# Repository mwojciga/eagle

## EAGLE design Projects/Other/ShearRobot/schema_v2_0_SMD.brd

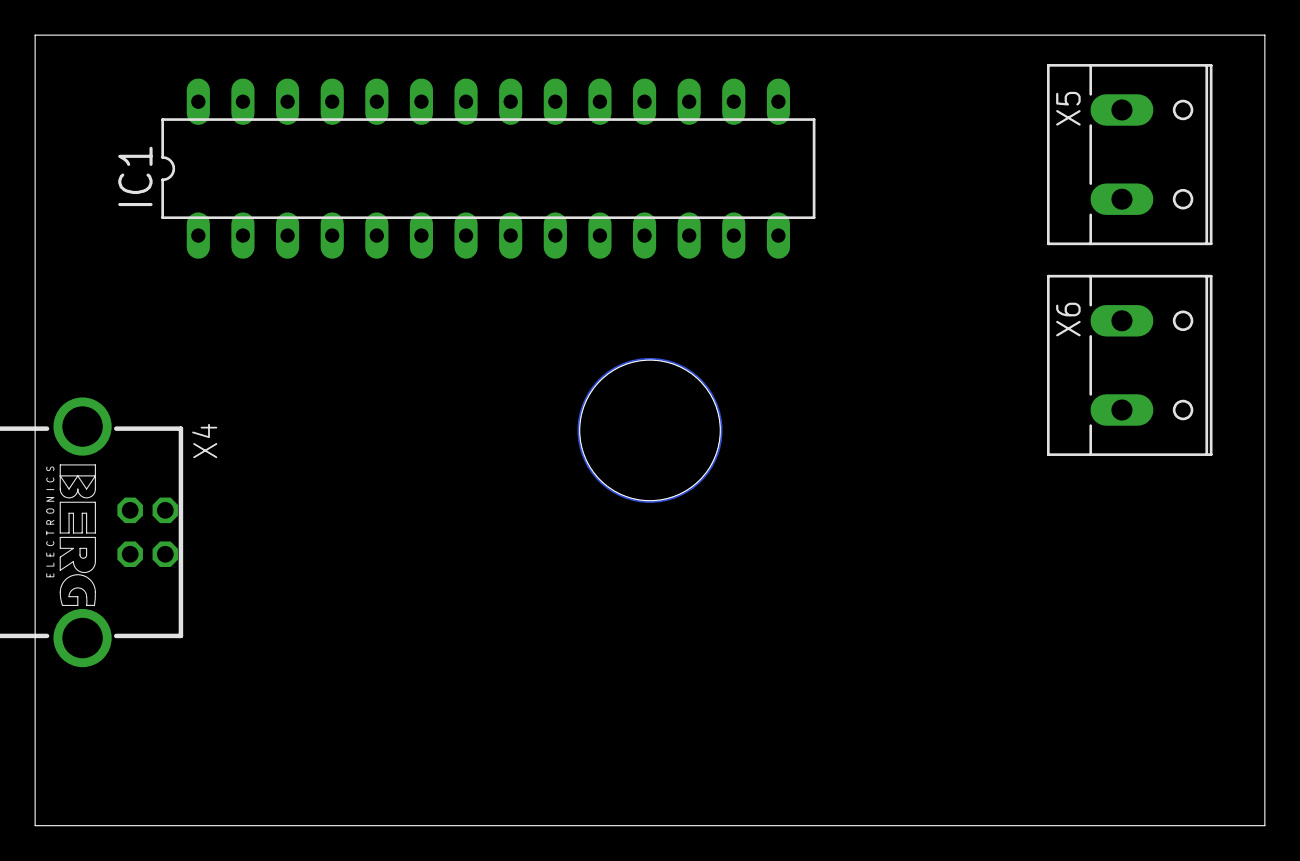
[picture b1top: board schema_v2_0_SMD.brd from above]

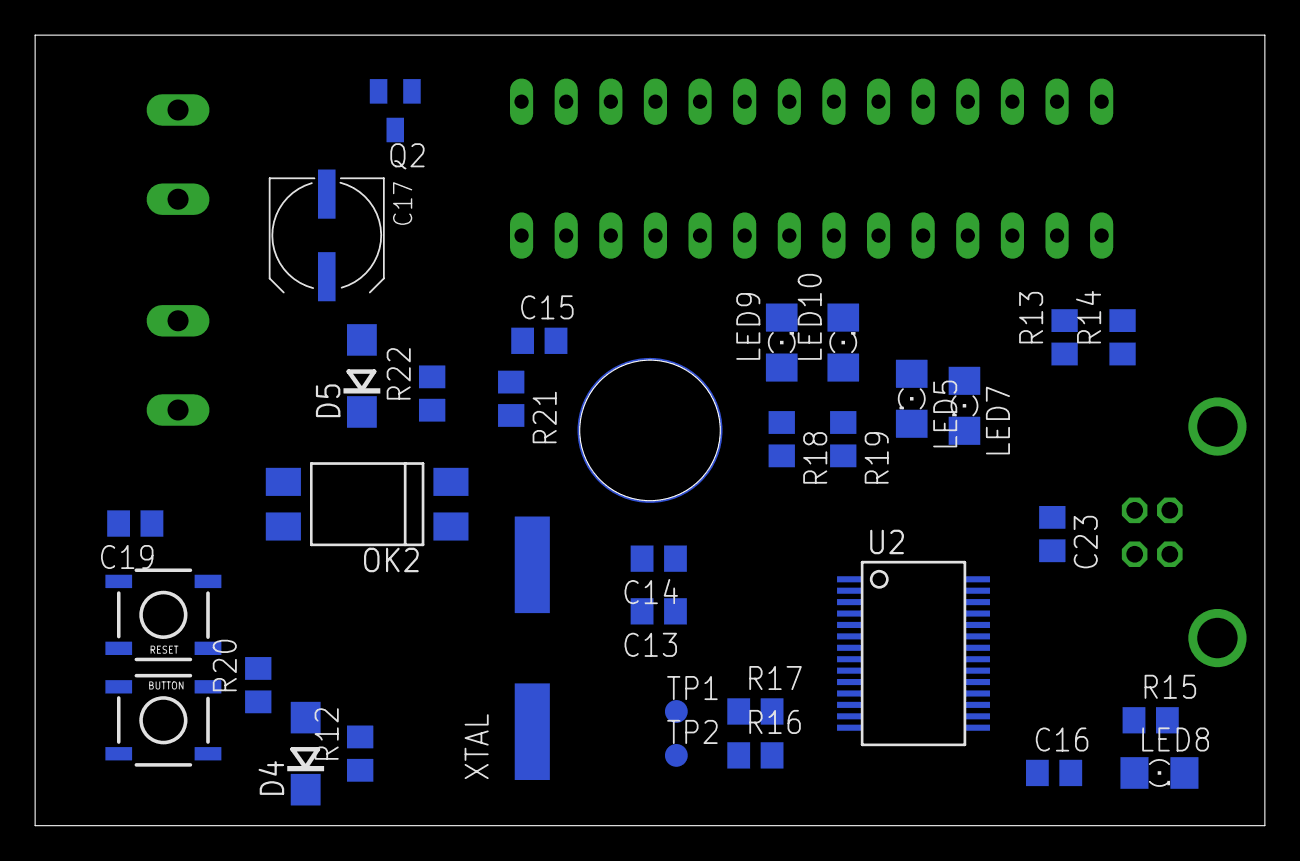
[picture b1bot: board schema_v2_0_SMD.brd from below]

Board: 2 copper layers, 70.0 x 45.0 mm, 37 parts (33 on the bottom side), 31 nets, no tracks yet.

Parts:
BUTTON: TACTILE_SWITCH_SMD
C13, C14: 22pF; C0805
C15, C16, C19, C23: 100nF; C0805
C17: UD-6,3X5,8_NICHICON
D4, D5: GS1B; DO214AC
IC1: MEGA8-P; DIL28-3
LED5, LED7, LED8, LED9, LED10: 1206
OK2: SFH6206; DIL4-SMD
Q2: BC817-16SMD; SOT23-BEC
R12: 22k; R0805
R13, R14, R15, R18, R19, R20: 330; R0805
R16, R17, R21: 1k; R0805
R22: 10k; R0805
RESET: TACTILE_SWITCH_SMD
TP1, TP2: TPTP13R; TP13R
U2: SSOP28DB
X4: PN61729-S
X5, X6: W237-132
XTAL: 16MHZ; CSM-7X-DU

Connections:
5V: C15.1, C23.2, D4.C, IC1.7, IC1.20, R12.1, R13.2, R14.2, R15.2, U2.4, U2.19, U2.20, X4.1
GND: BUTTON.1, BUTTON.2, C13.1, C14.1, C15.2, C16.2, C19.2, C23.1, IC1.8, IC1.22, LED8.C, LED9.C, LED10.C, OK2.2, RESET.3, RESET.4, U2.26, X4.4, X4.S1, X4.S2
unnamed: IC1.2, R16.1, TP2.TP
unnamed: IC1.3, R17.1, TP1.TP
unnamed: C19.1, IC1.21
unnamed: C14.2, IC1.10, XTAL.2
unnamed: C13.2, IC1.9, XTAL.1
unnamed: D4.A, IC1.1, R12.2, RESET.1, RESET.2
unnamed: LED5.A, R13.1
unnamed: LED7.A, R14.1
unnamed: LED5.C, U2.23
unnamed: LED7.C, U2.22
unnamed: R16.2, U2.5
unnamed: R17.2, U2.1
unnamed: BUTTON.3, BUTTON.4, R20.1
unnamed: IC1.6, R18.2
unnamed: U2.16, X4.2
unnamed: U2.15, X4.3
unnamed: IC1.5, R19.2
unnamed: LED8.A, R15.1
unnamed: IC1.23, R20.2
unnamed: C16.1, U2.17
unnamed: LED9.A, R18.1
unnamed: LED10.A, R19.1
unnamed: OK2.3, Q2.B
unnamed: OK2.1, R21.1
unnamed: IC1.11, R21.2
unnamed: OK2.4, R22.2
unnamed: C17.+, D5.C, R22.1, X5.2, X6.2
unnamed: C17.-, D5.A, Q2.C, X6.1
unnamed: Q2.E, X5.1

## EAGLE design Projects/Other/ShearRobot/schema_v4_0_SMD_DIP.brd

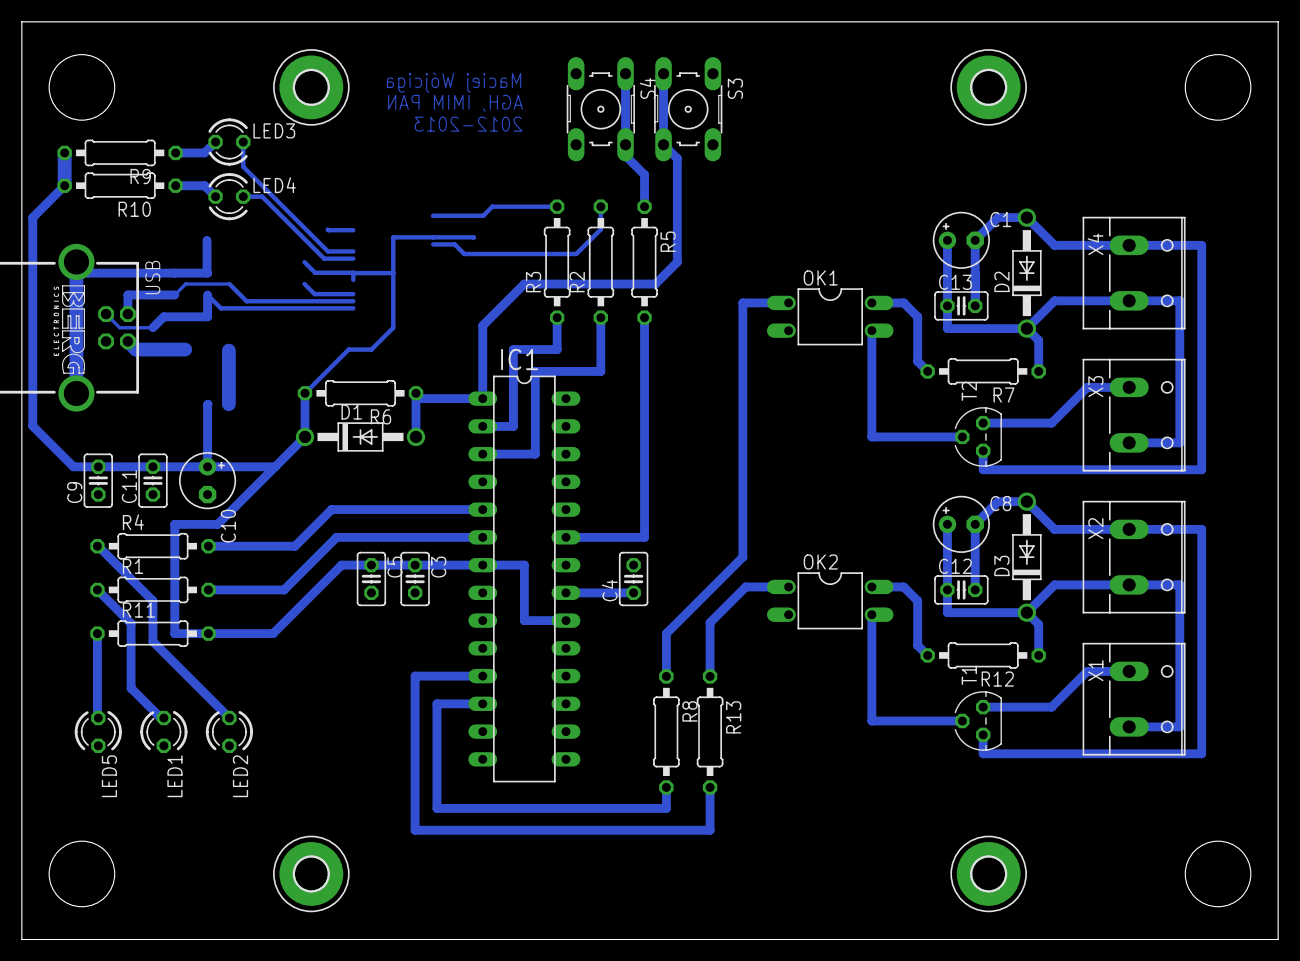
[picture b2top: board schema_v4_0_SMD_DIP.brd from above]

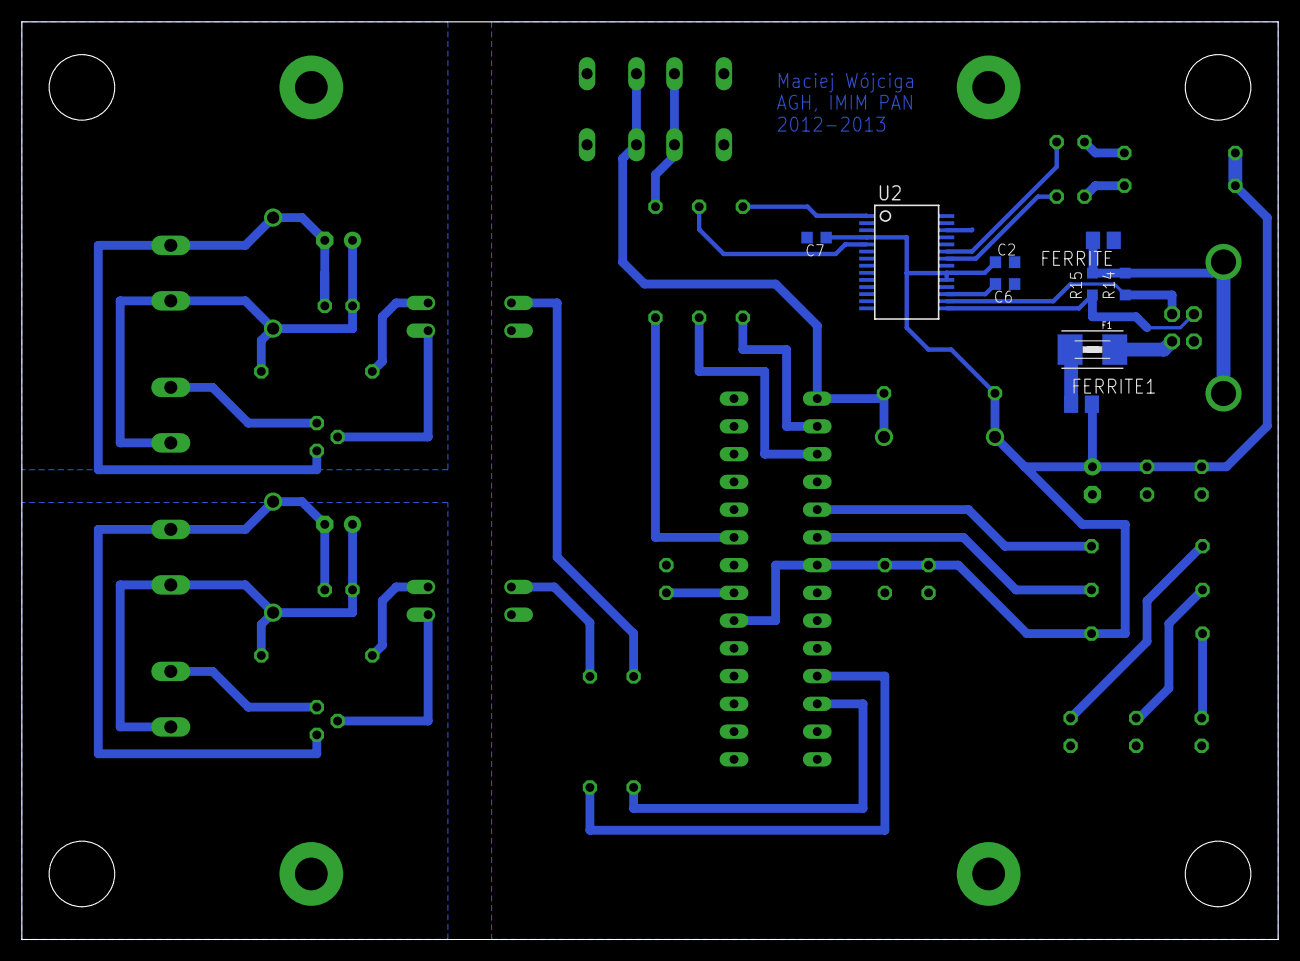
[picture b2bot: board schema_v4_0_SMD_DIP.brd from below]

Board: 2 copper layers, 115.0 x 84.0 mm, 56 parts (9 on the bottom side), 39 nets.

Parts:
C1, C8, C10: 1uF; E2,5-5
C2, C6, C7: 100nF; C0603K
C3, C4, C5, C9, C11, C12, C13: 100nF; C025-025X050
D1, D2, D3: 1N4001; DO41-10
F1: 1812
FERRITE, FERRITE1: M0805
H1, H2, H3, H4: MOUNT-PAD-ROUND3.0; 3,0-PAD
IC1: MEGA8-P; DIL28-3
LED1, LED2, LED3, LED4, LED5: LED3MM
OK1, OK2: LTV816; DIL04
R1, R4, R9, R10, R11: 330; 0207/10
R2, R3, R8, R13: 1k; 0207/10
R5, R7, R12: 10k; 0207/10
R6: 22k; 0207/10
R14, R15: VARISTORCN0603; CT/CN0603
S3, S4: B3F-10XX
T1, T2: BC547; TO92
U2: SSOP28DB
USB: PN61729-S
X1, X2, X3, X4: W237-132

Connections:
5V0: C2.1, C3.1, C5.1, C7.1, C9.2, C10.+, C11.2, D1.C, FERRITE1.2, IC1.7, IC1.20, R6.2, R9.2, R10.2, R11.2, U2.4, U2.19, U2.20
GND: C2.2, C3.2, C4.2, C5.2, C6.1, C7.2, C9.1, C10.-, C11.1, FERRITE.1, IC1.8, IC1.22, LED1.K, LED2.K, LED5.K, OK1.2, OK2.2, S3.1, S3.2, S4.3, S4.4, U2.26, USB.4
MOTOR1: IC1.11, R13.2
MOTOR2: IC1.12, R8.2
unnamed: IC1.3, R2.1
unnamed: IC1.2, R3.1
unnamed: C4.1, IC1.21
unnamed: IC1.23, R5.2
unnamed: LED1.A, R1.1
unnamed: LED2.A, R4.1
unnamed: D1.A, IC1.1, R6.1, S3.3, S3.4
unnamed: LED3.A, R9.1
unnamed: LED4.A, R10.1
unnamed: LED5.A, R11.1
unnamed: C1.+, C13.1, D2.C, R7.1, X3.2, X4.2
unnamed: OK2.1, R13.1
unnamed: C1.-, C13.2, D2.A, T2.3, X4.1
unnamed: OK1.3, T2.2
unnamed: OK2.4, R12.2
unnamed: T1.1, X1.1
unnamed: C8.+, C12.1, D3.C, R12.1, X1.2, X2.2
unnamed: C8.-, C12.2, D3.A, T1.3, X2.1
unnamed: OK2.3, T1.2
unnamed: F1.1, USB.1
unnamed: FERRITE.2, R14.2, R15.2, USB.S1, USB.S2
unnamed: F1.2, FERRITE1.1
unnamed: LED3.K, U2.23
unnamed: LED4.K, U2.22
unnamed: R5.1, S4.1, S4.2
unnamed: IC1.6, R1.2
unnamed: IC1.5, R4.2
unnamed: C6.2, U2.17
unnamed: OK1.1, R8.1
unnamed: OK1.4, R7.2
unnamed: T2.1, X3.1
RXD: R3.2, U2.1
TXD: R2.2, U2.5
USBDM: R14.1, U2.16, USB.2
USBDP: R15.1, U2.15, USB.3

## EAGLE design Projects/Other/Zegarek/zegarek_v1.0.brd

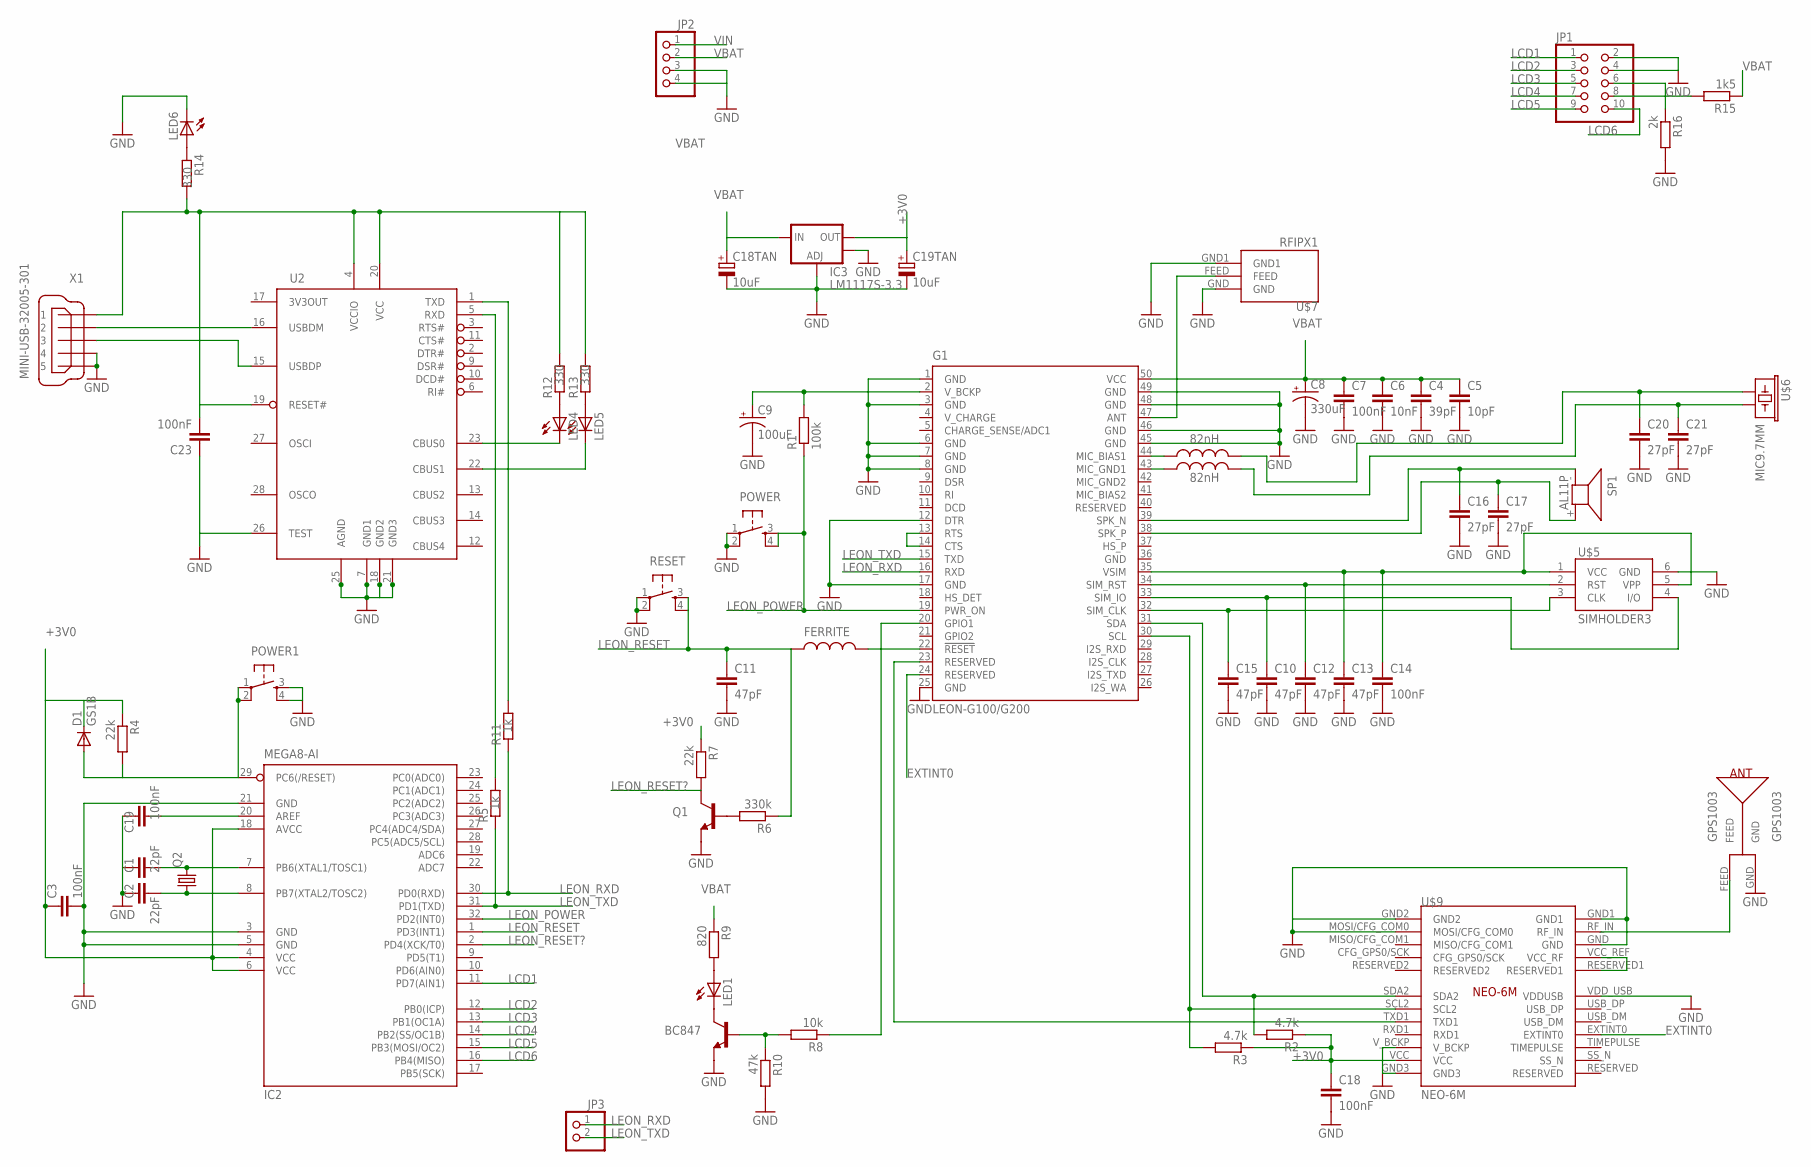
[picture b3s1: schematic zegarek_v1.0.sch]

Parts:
BC847: TRANSISTOR_NPNSOT23; SOT23
C1, C2: 22pF; C0805
C3, C7, C14, C18, C19, C23: 100nF; C0805
C4: 39pF; C0805
C5: 10pF; C0805
C6: 10nF; C0805
C8: 330uF; TT2D6
C9: 100uF; TT2D6
C10, C11, C12, C13, C15: 47pF; C0805
C16, C17, C20, C21: 27pF; C0805
C18TAN, C19TAN: 10uF; SMC_A
D1: GS1B; DO214AC
FERRITE: INDUCTOR0805; 0805
FERRITE1, FERRITE2: 82nH; 0805
G1: LEON-G100/G200
GPS1003: GPS1003
IC2: MEGA8-AI; TQFP32-08
IC3: LM1117S-3.3; SOT223
JP1: PINHD-2X5; 2X05
JP2: PINHD-1X4; 1X04
JP3: PINHD-1X2; 1X02
LED1, LED4, LED5, LED6: LEDSMT1206; 1206
POWER, POWER1: TAC_SWITCHSMD; TACTILE_SWITCH_SMD
Q1: TRANSISTOR_NPNSOT23; SOT23
Q2: CRYSTALHC49S; HC49/S
R1: 100k; R0805
R2, R3: 4.7k; R0805
R4, R7: 22k; R0805
R5, R11: 1k; R0805
R6: 330k; R0805
R8: 10k; R0805
R9: 820; R0805
R10: 47k; R0805
R12, R13, R14: 330; R0805
R15: 1k5; R0805
R16: 2k; R0805
RESET: TAC_SWITCHSMD; TACTILE_SWITCH_SMD
SP1: AL11P
U2: FT232RL; SSOP28DB
U$5: SIMHOLDER3
U$6: MIC9.7MM; MIC-9.7MM
U$7: RFIPX1; RF-IPX1
U$9: NEO-6M
X1: MINI-USB-32005-301; 32005-301

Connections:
+3V0: C3.1, C18.1, C19TAN.+, D1.C, IC2.4 (VCC), IC2.6 (VCC), IC2.18 (AVCC), IC3.2 (OUT), R2.1, R3.1, R4.1, R7.1, U$9.VCC
EXTINT0: G1.24 (RESERVED), U$9.EXTINT0
GND: BC847.2 (E), C1.1, C2.1, C3.2, C4.2, C5.2, C6.2, C7.2, C8.-, C9.-, C10.2, C11.2, C12.2, C13.2, C14.2, C15.2, C16.2, C17.2, C18.2, C18TAN.-, C19.2, C19TAN.-, C20.2, C21.2, C23.1, G1.1 (GND), G1.3 (GND), G1.6 (GND), G1.7 (GND), G1.8 (GND), G1.12 (DTR), G1.17 (GND), G1.25 (GND), G1.36 (GND), G1.45 (GND), G1.46 (GND), G1.48 (GND), G1.49 (GND), GPS1003.GND, IC2.3 (GND), IC2.5 (GND), IC2.21 (GND), IC3.1 (ADJ), IC3.4 (OUT), JP1.2, JP1.4, JP2.3, LED6.C, POWER.1, POWER.2, POWER1.3, POWER1.4, Q1.2 (E), R10.2, R16.2, RESET.1, RESET.2, U2.7 (GND1), U2.18 (GND2), U2.21 (GND3), U2.25 (AGND), U2.26 (TEST), U$5.6 (GND), U$7.GND, U$7.GND1, U$9.GND, U$9.GND1, U$9.GND2, U$9.GND3, U$9.MOSI/CFG_COM0, U$9.VDD_USB (VDDUSB), U$9.V_BCKP, X1.4, X1.5
LCD1: IC2.11 (PD7(AIN1)), JP1.1
LCD2: IC2.12 (PB0(ICP)), JP1.3
LCD3: IC2.13 (PB1(OC1A)), JP1.5
LCD4: IC2.14 (PB2(SS/OC1B)), JP1.7
LCD5: IC2.15 (PB3(MOSI/OC2)), JP1.9
LCD6: IC2.16 (PB4(MISO)), JP1.10
LEON_POWER: G1.19 (PWR_ON), IC2.32 (PD2(INT0)), POWER.3, POWER.4, R1.1
LEON_RESET: C11.1, FERRITE.1, IC2.1 (PD3(INT1)), R6.1, RESET.3, RESET.4
LEON_RESET?: IC2.2 (PD4(XCK/T0)), Q1.3 (C), R7.2
LEON_RXD: G1.16 (RXD), IC2.30 (PD0(RXD)), JP3.1, R11.1
LEON_TXD: G1.15 (TXD), IC2.31 (PD1(TXD)), JP3.2, R5.1
unnamed: FERRITE.2, G1.22 (!RESET)
unnamed: C2.2, IC2.8 (PB7(XTAL2/TOSC2)), Q2.1
unnamed: C9.+, G1.2 (V_BCKP), R1.2
unnamed: C13.1, C14.1, G1.35 (VSIM), U$5.1 (VCC), U$5.5 (VPP)
unnamed: C15.1, G1.32 (SIM_CLK), U$5.3 (CLK)
unnamed: C12.1, G1.34 (SIM_RST), U$5.2 (RST)
unnamed: C16.1, G1.39 (SPK_N), SP1.- (1)
unnamed: C10.1, G1.33 (SIM_IO), U$5.4 (I/O)
unnamed: C17.1, G1.38 (SPK_P), SP1.+ (2)
unnamed: G1.13 (RTS), G1.14 (CTS)
unnamed: FERRITE1.1, G1.44 (MIC_BIAS1)
unnamed: FERRITE2.1, G1.43 (MIC_GND1)
unnamed: C20.1, FERRITE1.2, U$6.1
unnamed: C21.1, FERRITE2.2, U$6.2
unnamed: Q1.1 (B), R6.2
unnamed: BC847.1 (B), R8.2, R10.1
unnamed: LED1.A, R9.2
unnamed: BC847.3 (C), LED1.C
unnamed: G1.20 (GPIO1), R8.1
unnamed: G1.47 (ANT), U$7.FEED
unnamed: JP1.6, R16.1
unnamed: GPS1003.FEED, U$9.RF_IN
unnamed: G1.31 (SDA), R2.2, U$9.SDA2
unnamed: U$9.RESERVED1, U$9.VCC_REF (VCC_RF)
unnamed: G1.30 (SCL), R3.2, U$9.SCL2
unnamed: G1.23 (RESERVED), U$9.TXD1
unnamed: C1.2, IC2.7 (PB6(XTAL1/TOSC1)), Q2.2
unnamed: D1.A, IC2.29 (PC6(/RESET)), POWER1.1, POWER1.2, R4.2
unnamed: C19.1, IC2.20 (AREF)
unnamed: LED4.A, R12.1
unnamed: LED5.A, R13.1
unnamed: LED4.C, U2.23 (CBUS0)
unnamed: LED5.C, U2.22 (CBUS1)
unnamed: R11.2, U2.1 (TXD)
unnamed: R5.2, U2.5 (RXD)
unnamed: JP1.8, R15.2
unnamed: C23.2, R12.2, R13.2, R14.2, U2.4 (VCCIO), U2.19 (RESET#), U2.20 (VCC), X1.1
unnamed: U2.16 (USBDM), X1.2
unnamed: U2.15 (USBDP), X1.3
unnamed: LED6.A, R14.1
VBAT: C4.1, C5.1, C6.1, C7.1, C8.+, C18TAN.+, G1.50 (VCC), IC3.3 (IN), JP2.2, R9.1, R15.1
VIN: JP2.1

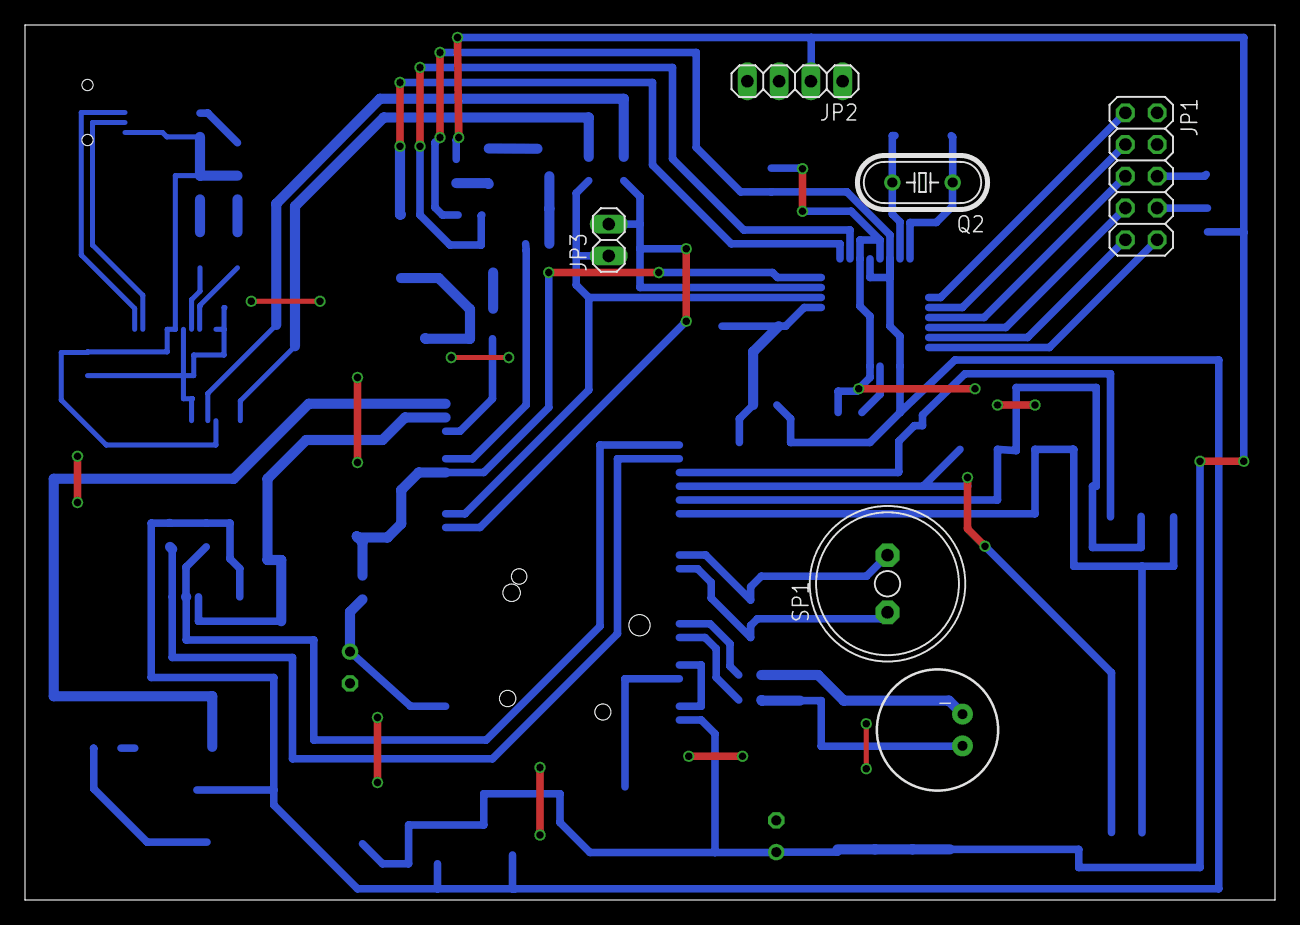
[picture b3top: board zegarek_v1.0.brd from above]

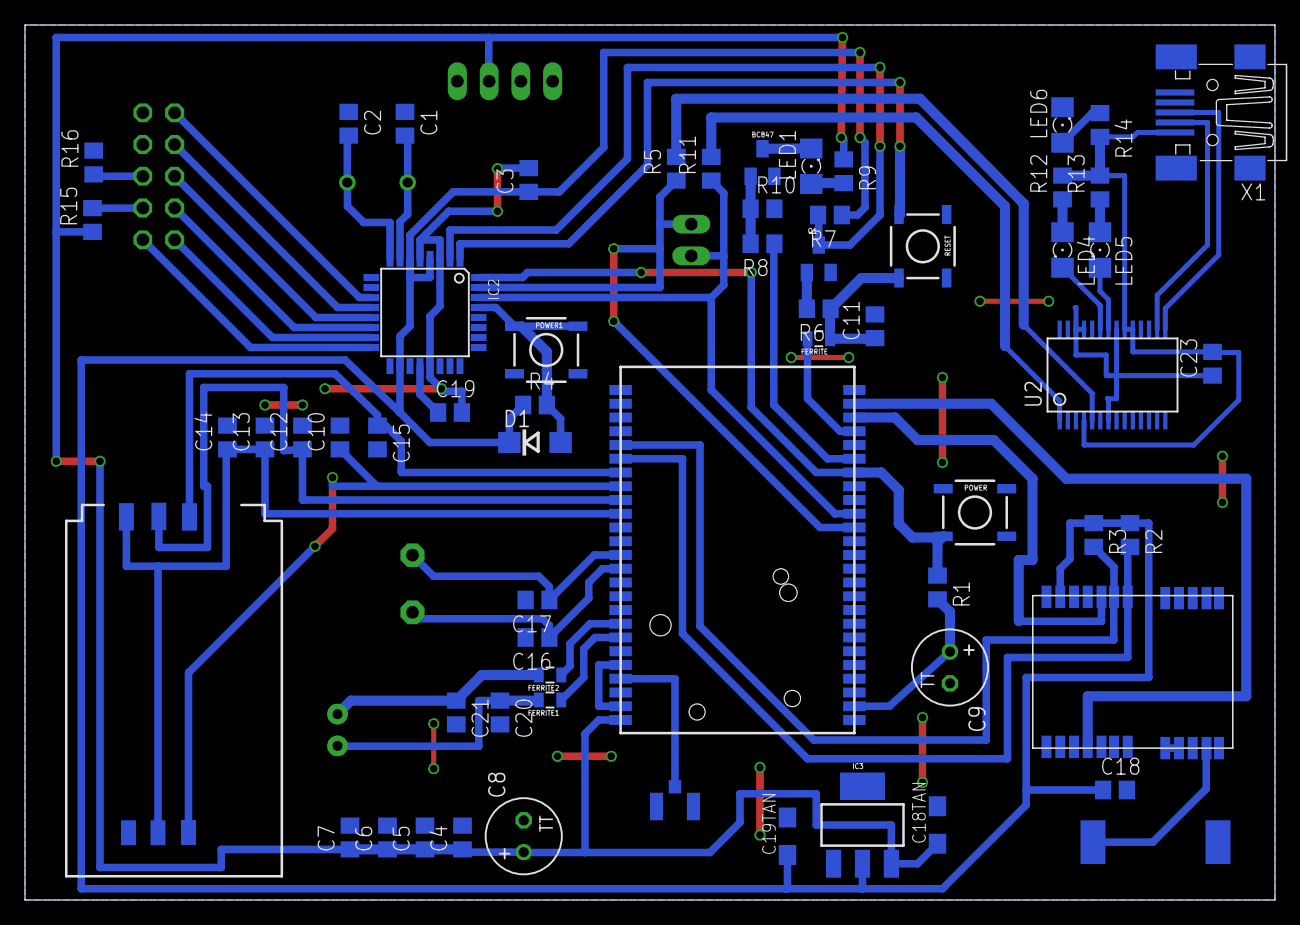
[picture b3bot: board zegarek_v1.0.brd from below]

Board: 2 copper layers, 100.0 x 70.0 mm, 68 parts (62 on the bottom side), 55 nets.

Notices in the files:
parts and their libraries:
SparkFun: Licensing: CC v3.0 Share-Alike You are welcome to use this library for commercial purposes.
